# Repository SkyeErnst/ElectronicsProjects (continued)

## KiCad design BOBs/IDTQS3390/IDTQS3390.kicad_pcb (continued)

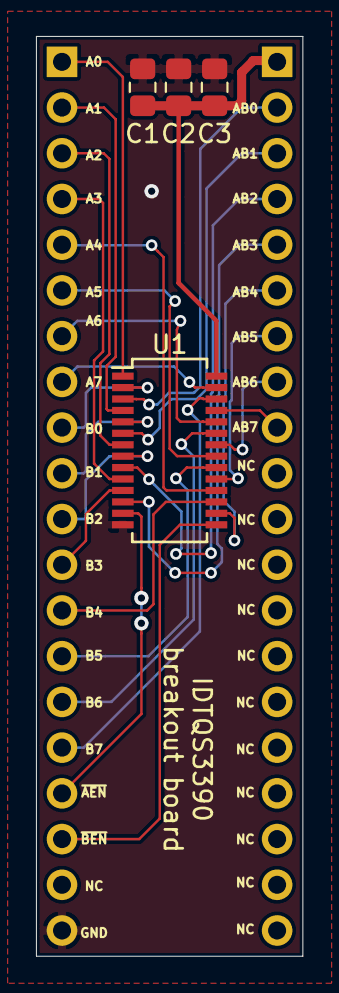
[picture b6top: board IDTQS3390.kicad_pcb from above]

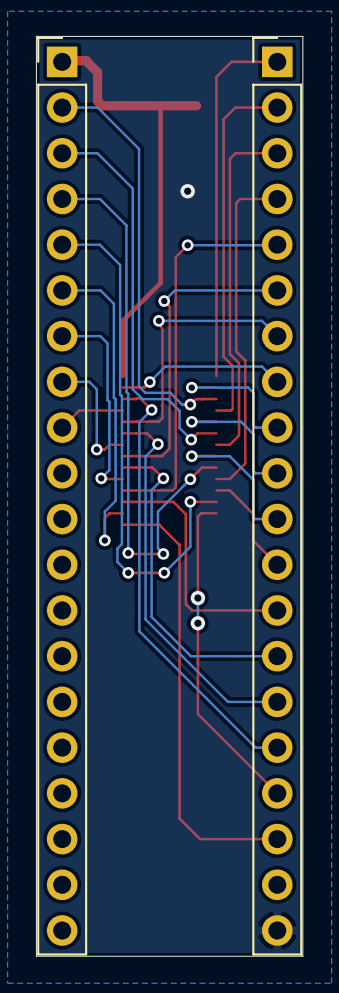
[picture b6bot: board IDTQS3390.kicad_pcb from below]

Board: 2 copper layers, 14.8 x 51.1 mm, 6 parts (2 on the bottom side), 28 nets.

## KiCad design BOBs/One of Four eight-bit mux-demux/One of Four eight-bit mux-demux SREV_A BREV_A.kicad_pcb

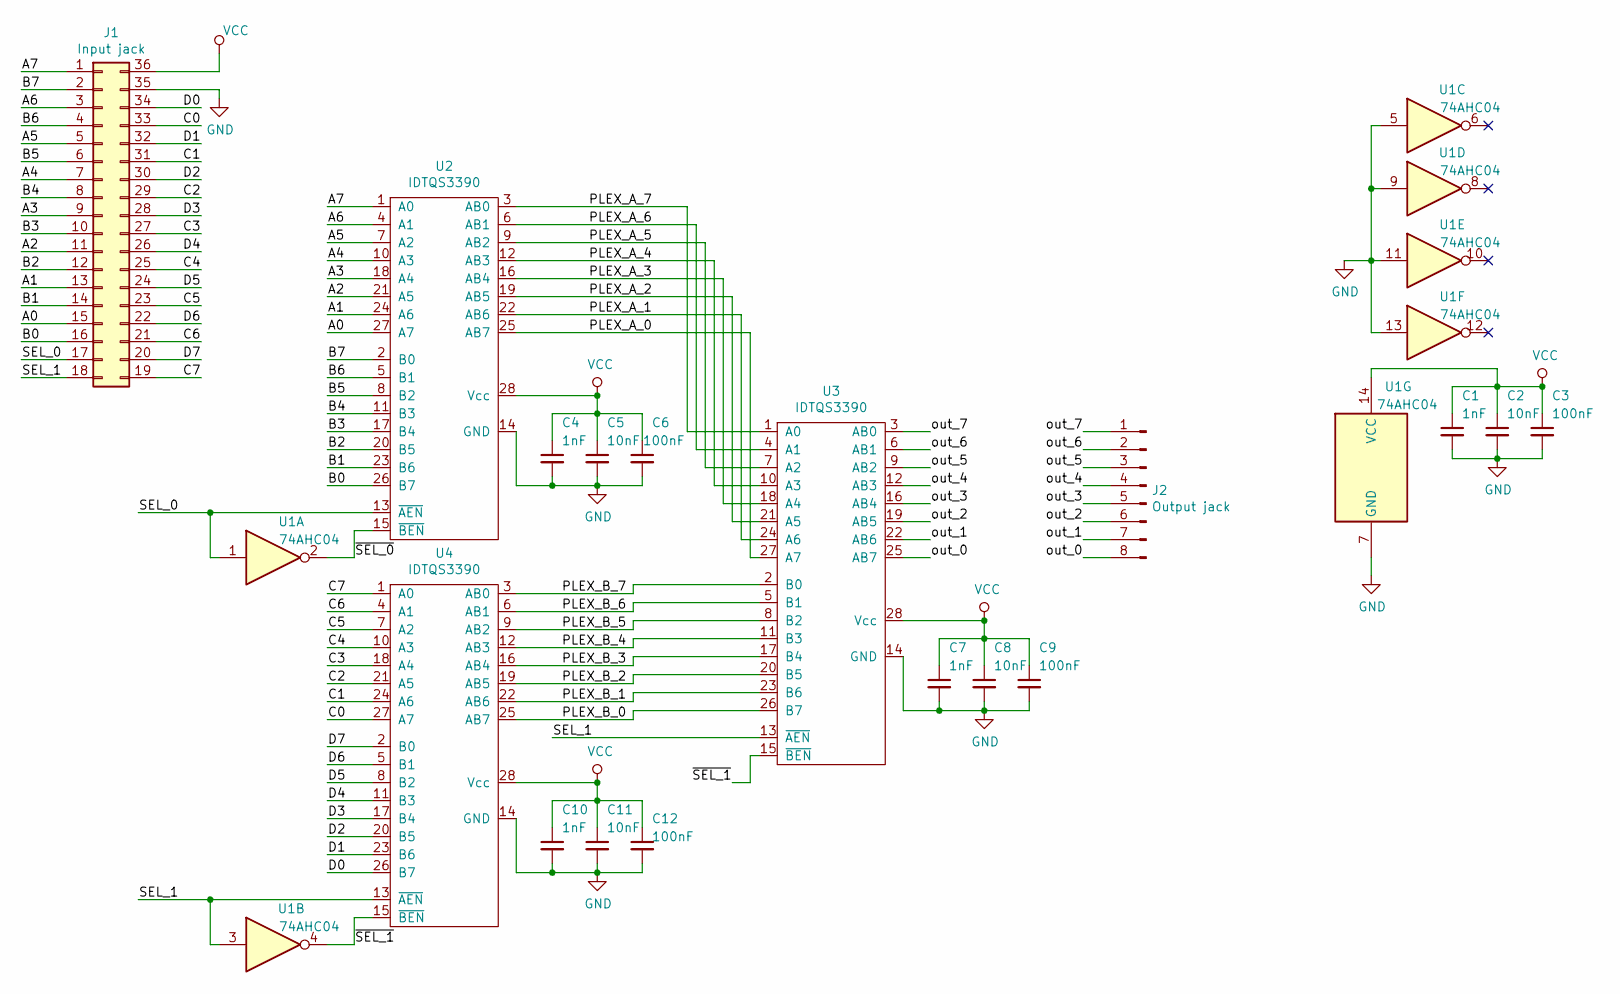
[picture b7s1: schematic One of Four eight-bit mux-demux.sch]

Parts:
C1, C4, C7, C10: 1nF; C_0805_2012Metric_Pad1.15x1.40mm_HandSolder
C2, C5, C8, C11: 10nF; C_0805_2012Metric_Pad1.15x1.40mm_HandSolder
C3, C6, C9, C12: 100nF; C_0805_2012Metric_Pad1.15x1.40mm_HandSolder
J1: Input jack; PinHeader_2x18_P2.54mm_Vertical
J2: Output jack; PinHeader_1x08_P2.54mm_Vertical
U1: 74AHC04; SOIC-14_3.9x8.7mm_P1.27mm
U2, U3, U4: IDTQS3390; SSOP-28_3.9x9.9mm_P0.635mm

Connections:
/A0: J1.15, U2.27 (A7)
/A1: J1.13, U2.24 (A6)
/A2: J1.11, U2.21 (A5)
/A3: J1.9, U2.18 (A4)
/A4: J1.7, U2.10 (A3)
/A5: J1.5, U2.7 (A2)
/A6: J1.3, U2.4 (A1)
/A7: J1.1, U2.1 (A0)
/B0: J1.16, U2.26 (B7)
/B1: J1.14, U2.23 (B6)
/B2: J1.12, U2.20 (B5)
/B3: J1.10, U2.17 (B4)
/B4: J1.8, U2.11 (B3)
/B5: J1.6, U2.8 (B2)
/B6: J1.4, U2.5 (B1)
/B7: J1.2, U2.2 (B0)
/C0: J1.33, U4.27 (A7)
/C1: J1.31, U4.24 (A6)
/C2: J1.29, U4.21 (A5)
/C3: J1.27, U4.18 (A4)
/C4: J1.25, U4.10 (A3)
/C5: J1.23, U4.7 (A2)
/C6: J1.21, U4.4 (A1)
/C7: J1.19, U4.1 (A0)
/D0: J1.34, U4.26 (B7)
/D1: J1.32, U4.23 (B6)
/D2: J1.30, U4.20 (B5)
/D3: J1.28, U4.17 (B4)
/D4: J1.26, U4.11 (B3)
/D5: J1.24, U4.8 (B2)
/D6: J1.22, U4.5 (B1)
/D7: J1.20, U4.2 (B0)
/PLEX_A_0: U2.3 (AB0), U3.1 (A0)
/PLEX_A_1: U2.6 (AB1), U3.4 (A1)
/PLEX_A_2: U2.9 (AB2), U3.7 (A2)
/PLEX_A_3: U2.12 (AB3), U3.10 (A3)
/PLEX_A_4: U2.16 (AB4), U3.18 (A4)
/PLEX_A_5: U2.19 (AB5), U3.21 (A5)
/PLEX_A_6: U2.22 (AB6), U3.24 (A6)
/PLEX_A_7: U2.25 (AB7), U3.27 (A7)
/PLEX_B_0: U3.2 (B0), U4.3 (AB0)
/PLEX_B_1: U3.5 (B1), U4.6 (AB1)
/PLEX_B_2: U3.8 (B2), U4.9 (AB2)
/PLEX_B_3: U3.11 (B3), U4.12 (AB3)
/PLEX_B_4: U3.17 (B4), U4.16 (AB4)
/PLEX_B_5: U3.20 (B5), U4.19 (AB5)
/PLEX_B_6: U3.23 (B6), U4.22 (AB6)
/PLEX_B_7: U3.26 (B7), U4.25 (AB7)
/SEL_0: J1.17, U1.1, U2.13 (~AEN)
/SEL_1: J1.18, U1.3, U3.13 (~AEN), U4.13 (~AEN)
/out_0: J2.8, U3.25 (AB7)
/out_1: J2.7, U3.22 (AB6)
/out_2: J2.6, U3.19 (AB5)
/out_3: J2.5, U3.16 (AB4)
/out_4: J2.4, U3.12 (AB3)
/out_5: J2.3, U3.9 (AB2)
/out_6: J2.2, U3.6 (AB1)
/out_7: J2.1, U3.3 (AB0)
/~SEL_0: U1.2, U2.15 (~BEN)
/~SEL_1: U1.4, U3.15 (~BEN), U4.15 (~BEN)
GND: C1.2, C2.2, C3.2, C4.2, C5.2, C6.2, C7.2, C8.2, C9.2, C10.2, C11.2, C12.2, J1.35, U1.5, U1.7 (GND), U1.9, U1.11, U1.13, U2.14 (GND), U3.14 (GND), U4.14 (GND)
VCC: C1.1, C2.1, C3.1, C4.1, C5.1, C6.1, C7.1, C8.1, C9.1, C10.1, C11.1, C12.1, J1.36, U1.14 (VCC), U2.28 (Vcc), U3.28 (Vcc), U4.28 (Vcc)

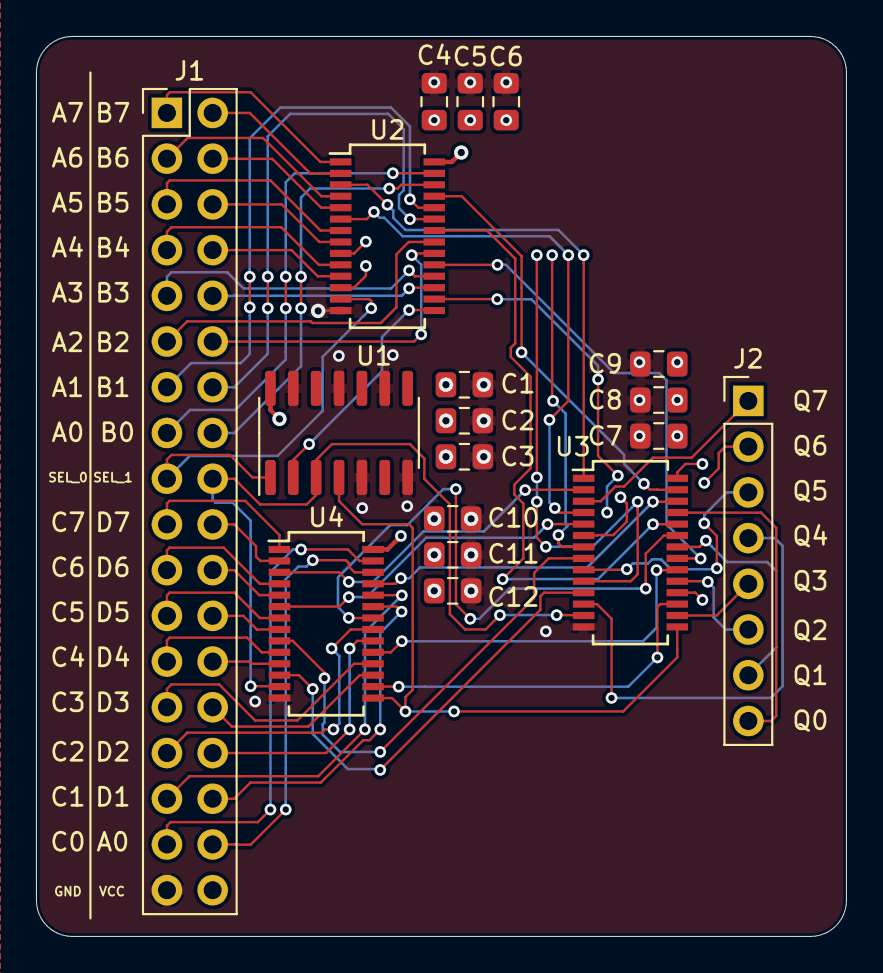
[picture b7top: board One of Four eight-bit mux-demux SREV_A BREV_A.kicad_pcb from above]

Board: 4 copper layers, 45.0 x 50.0 mm, 18 parts (0 on the bottom side), 62 nets.
